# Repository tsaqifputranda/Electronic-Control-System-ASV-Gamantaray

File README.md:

# 🔧 Electronic (Control System) - ASV Gamantaray

Selamat datang di dokumentasi sistem kontrol elektronika kapal otonom Gamantaray.

## 📋 Daftar Isi Dokumentasi
1. **Project Overview** (Halaman Utama)
2. [Spesifikasi Sistem (Requirements)](./02_Requirements/requirements.md)
3. [Arsitektur & Diagram Blok](./03_System_Architecture/architecture.md)
4. [Desain Hardware & PCB](./04_Hardware_Design/hardware_desain.md)
5. [Power Management](./05_Power_Management/power_management.md)
6. [Wiring & Integration](./06_Wiring_&_Integration/integration_notes.md)
7. [Testing](./07_Testing/test_procedures.md)
8. [Problem & Solution](./08_Problem_&_Solution/troubleshooting.md)
9. [Final Evaluation](./09_Final_Evaluation/final_evaluation.md)
10. [Next Generation Notes](./10_Next_Generation_Notes/next_generation_notes.md)

---

## 🔌 Diagram Blok Sistem Utama
Untuk gambaran cepat mengenai interkoneksi sistem, kamu bisa melihat ringkasan diagram melalui tautan di bawah ini:

* ⚡ [Buka Diagram Blok Distribusi Daya Sistem Kontrol](./03_System_Architecture/PDB_Control_System_Diagram.jpg)
* 🗺️ [Buka Diagram Arsitektur Komunikasi Antar Komponen](./03_System_Architecture/Communication_Architecture_Diagram.jpg)

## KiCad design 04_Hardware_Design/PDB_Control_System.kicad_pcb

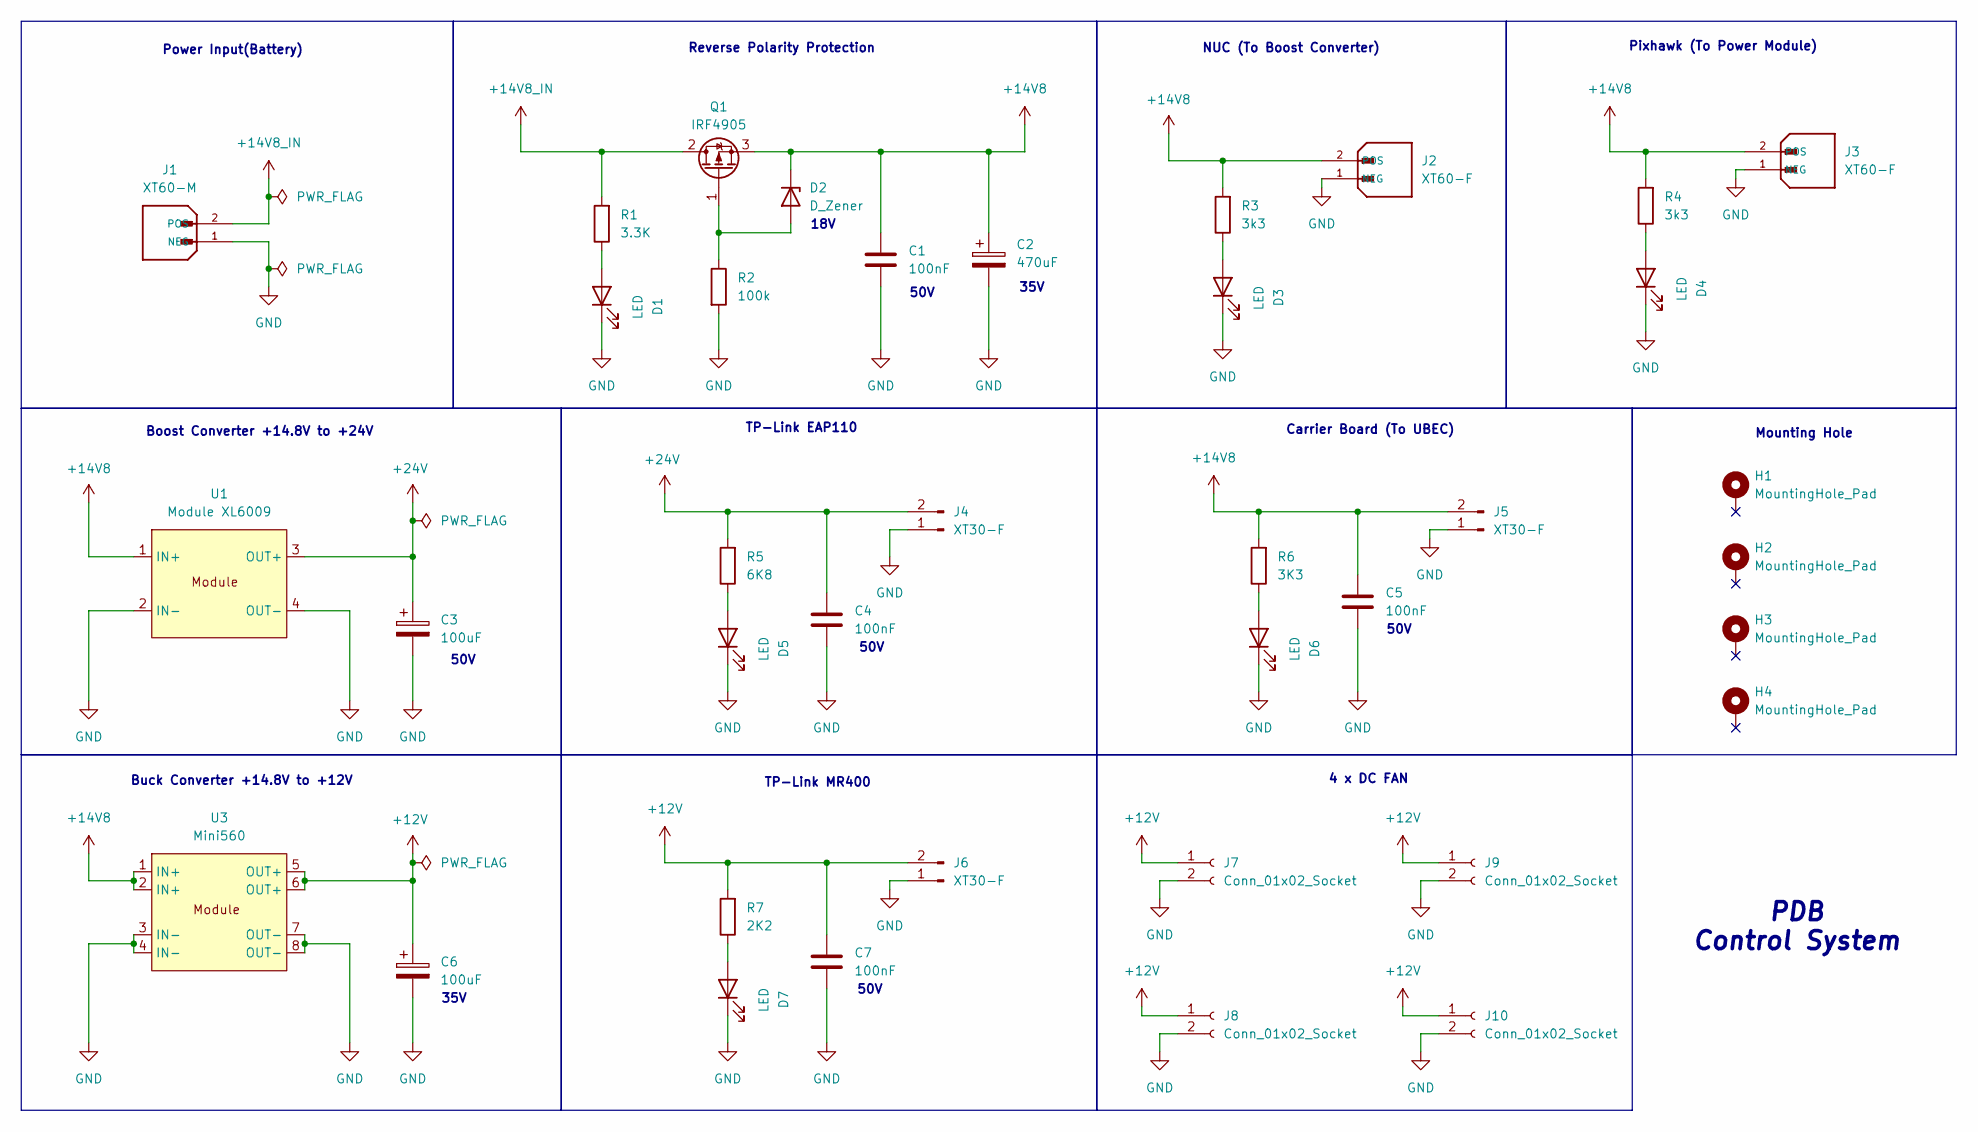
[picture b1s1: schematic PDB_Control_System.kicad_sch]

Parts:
C1, C4, C5, C7: 100nF; C_0805_2012Metric_Pad1.18x1.45mm_HandSolder
C2: 470uF; CP_Elec_10x10
C3, C6: 100uF; CP_Elec_6.3x5.4
D1, D3, D4, D5, D6, D7: LED; LED_0805_2012Metric_Pad1.15x1.40mm_HandSolder
D2: D_Zener; D_SOD-123
H1, H2, H3, H4: MountingHole_Pad; MountingHole_3.2mm_M3_Pad
J1: XT60-M; AMASS_XT60-M_1x02_P7.20mm_Vertical; PARTREV V1.2
J2, J3: XT60-F; AMASS_XT60-F_1x02_P7.20mm_Vertical
J4, J5, J6: XT30-F; AMASS_XT30U-F_1x02_P5.0mm_Vertical_custom
J7, J8, J9, J10: Conn_01x02_Socket; JST_XH_B2B-XH-A_1x02_P2.50mm_Vertical
Q1: IRF4905; TO-263-2
R1: 3.3K; R_0805_2012Metric_Pad1.20x1.40mm_HandSolder
R2: 100k; R_0805_2012Metric_Pad1.20x1.40mm_HandSolder
R3, R4: 3k3; R_0805_2012Metric_Pad1.20x1.40mm_HandSolder
R5: 6K8; R_0805_2012Metric_Pad1.20x1.40mm_HandSolder
R6: 3K3; R_0805_2012Metric_Pad1.20x1.40mm_HandSolder
R7: 2K2; R_0805_2012Metric_Pad1.20x1.40mm_HandSolder
U1: Module XL6009; XL6009 Module
U3: Mini560; Module Mini560

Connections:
+12V: C6.1, C7.1, J6.2, J7.1, J8.1, J9.1, J10.1, R7.2, U3.5 (OUT+), U3.6 (OUT+)
+14V8: C1.1, C2.1, C5.1, D2.1 (K), J2.2 (POS), J3.2 (POS), J5.2, Q1.3 (S), R3.2, R4.2, R6.2, U1.1 (IN+), U3.1 (IN+), U3.2 (IN+)
+14V8_IN: J1.2 (POS), Q1.2 (D), R1.2
+24V: C3.1, C4.1, J4.2, R5.2, U1.3 (OUT+)
GND: C1.2, C2.2, C3.2, C4.2, C5.2, C6.2, C7.2, D1.1 (K), D3.1 (K), D4.1 (K), D5.1 (K), D6.1 (K), D7.1 (K), J1.1 (NEG), J2.1 (NEG), J3.1 (NEG), J4.1, J5.1, J6.1, J7.2, J8.2, J9.2, J10.2, R2.2, U1.2 (IN-), U1.4 (OUT-), U3.3 (IN-), U3.4 (IN-), U3.7 (OUT-), U3.8 (OUT-)
unnamed: D1.2 (A), R1.1
unnamed: D2.2 (A), Q1.1 (G), R2.1
unnamed: D3.2 (A), R3.1
unnamed: D4.2 (A), R4.1
unnamed: D5.2 (A), R5.1
unnamed: D6.2 (A), R6.1
unnamed: D7.2 (A), R7.1

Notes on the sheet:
50V
18V
NUC (To Boost Converter)
Buck Converter +14.8V to +12V
4 x DC FAN
Boost Converter +14.8V to +24V
TP-Link EAP110
35V
Mounting Hole
Pixhawk (To Power Module)
Reverse Polarity Protection
PDB Control System
Power Input(Battery)
Carrier Board (To UBEC)
TP-Link MR400

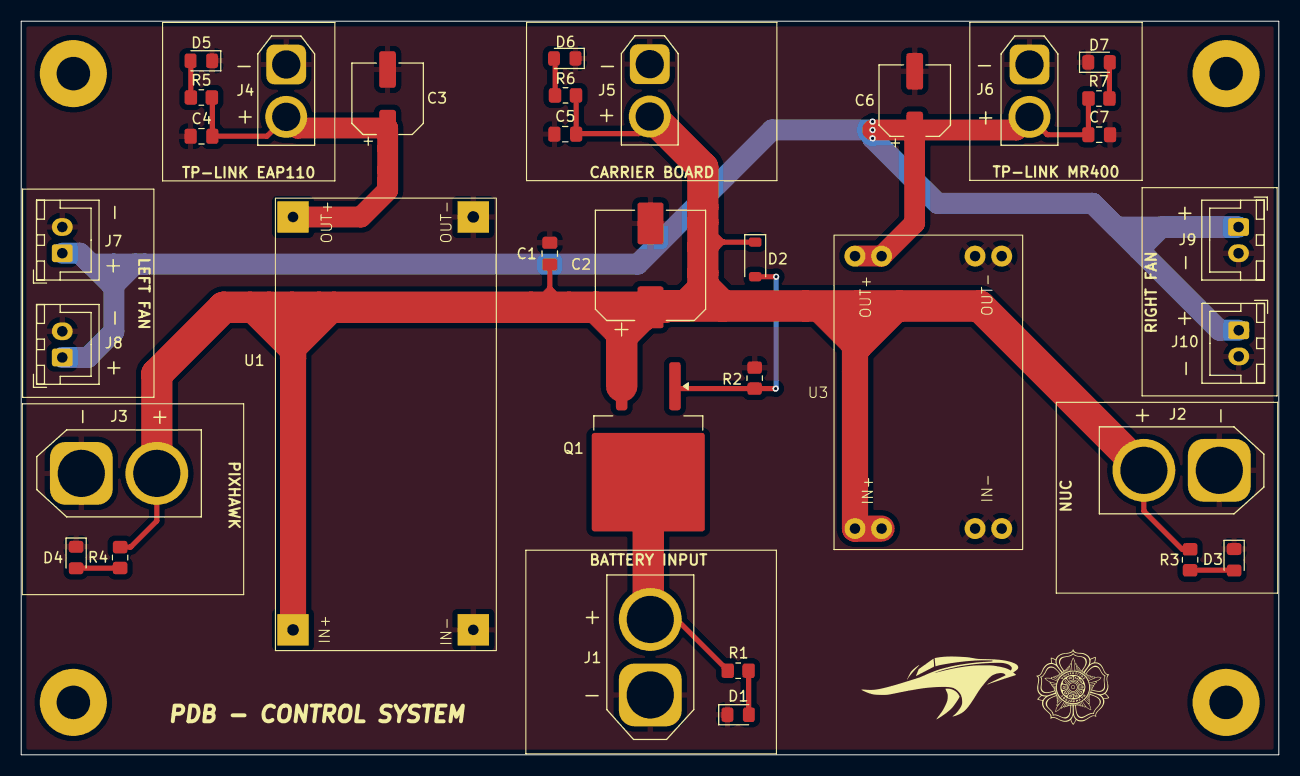
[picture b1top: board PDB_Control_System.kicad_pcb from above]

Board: 2 copper layers, 120.0 x 70.0 mm, 38 parts (0 on the bottom side), 12 nets.

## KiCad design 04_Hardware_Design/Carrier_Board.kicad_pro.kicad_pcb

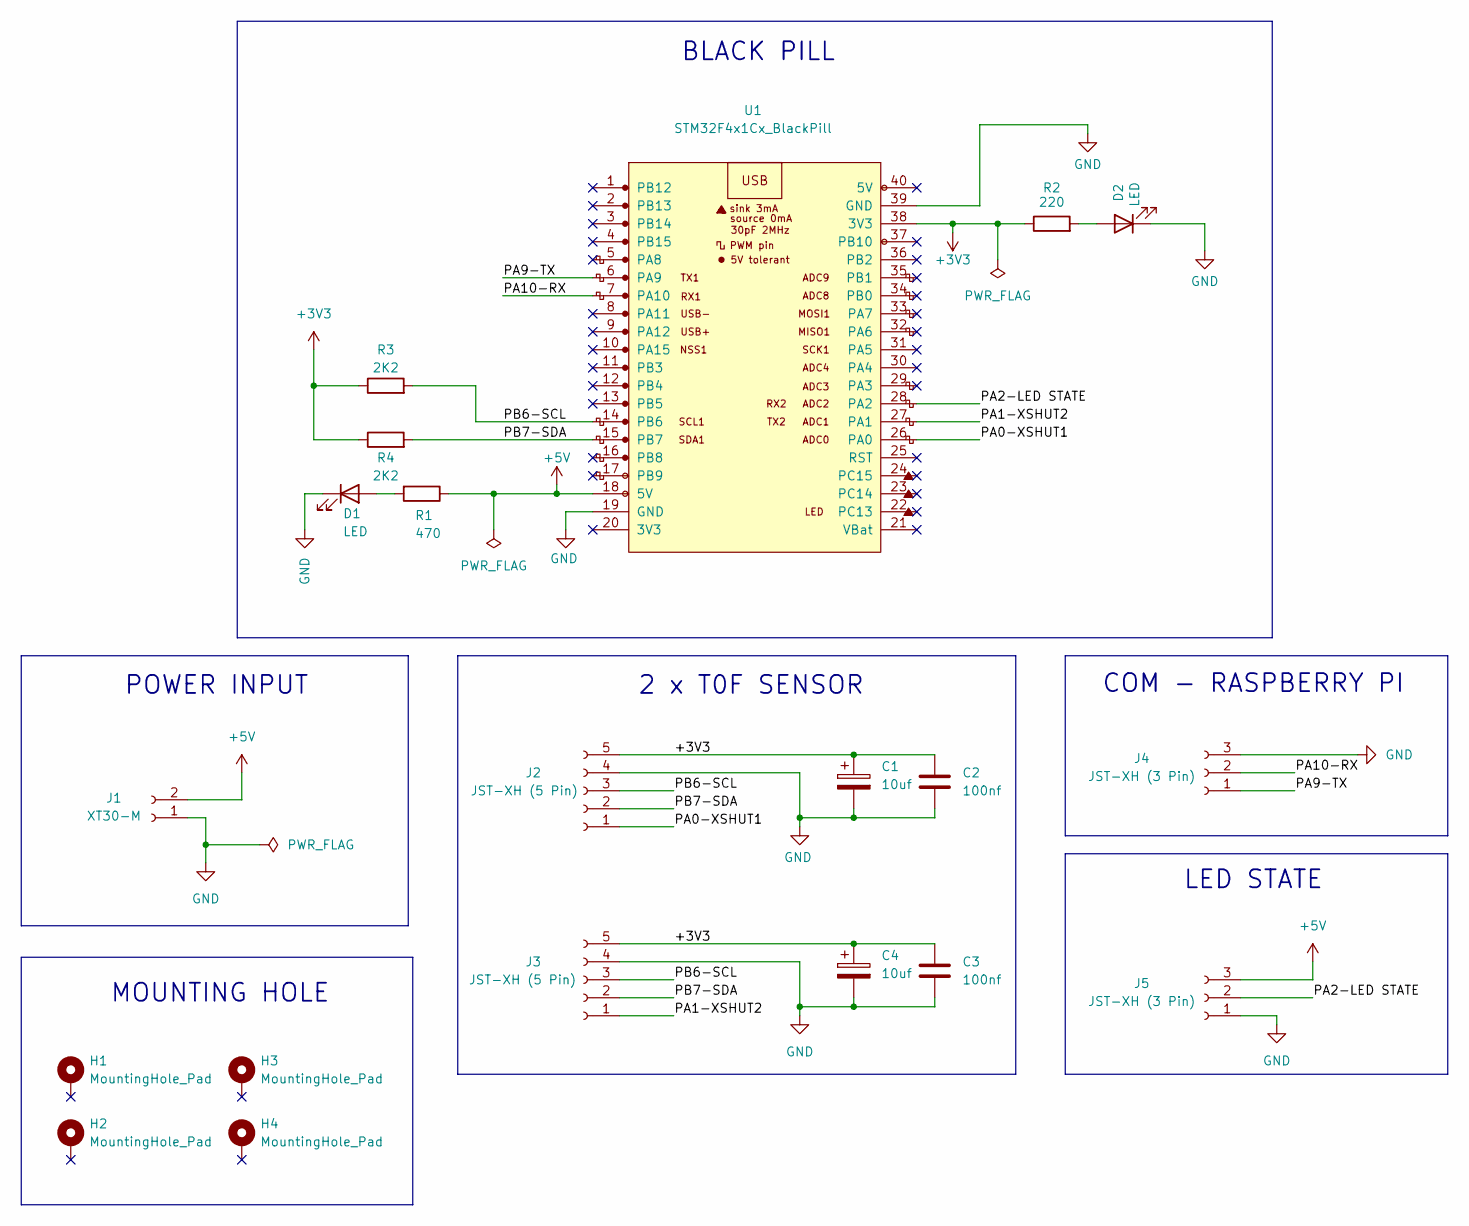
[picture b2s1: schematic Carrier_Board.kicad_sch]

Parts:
C1, C4: 10uf; CP_Elec_4x5.3
C2, C3: 100nf; C_0805_2012Metric_Pad1.18x1.45mm_HandSolder
D1, D2: LED; LED_0805_2012Metric
H1, H2, H3, H4: MountingHole_Pad; MountingHole_3.2mm_M3_Pad
J1: XT30-M; AMASS_XT30U-M_1x02_P5.0mm_Vertical
J2, J3: JST-XH (5 Pin); JST_XH_B5B-XH-A_1x05_P2.50mm_Vertical
J4, J5: JST-XH (3 Pin); JST_XH_B3B-XH-A_1x03_P2.50mm_Vertical
R1: 470; R_0805_2012Metric_Pad1.20x1.40mm_HandSolder
R2: 220; R_0805_2012Metric_Pad1.20x1.40mm_HandSolder
R3, R4: 2K2; R_0805_2012Metric_Pad1.20x1.40mm_HandSolder
U1: STM32F4x1Cx_BlackPill; STM32F4x1Cx_BlackPill_PartLike

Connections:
+3V3: C1.1, C2.1, C3.1, C4.1, J2.5, J3.5, R2.1, R3.1, R4.1, U1.38 (3V3)
+5V: J1.2, J5.3, R1.1, U1.18 (5V)
/PA0-XSHUT1: J2.1, U1.26 (PA0)
/PA1-XSHUT2: J3.1, U1.27 (PA1)
/PA2-LED STATE: J5.2, U1.28 (PA2)
/PA9-TX: J4.1, U1.6 (PA9)
/PA10-RX: J4.2, U1.7 (PA10)
/PB6-SCL: J2.3, J3.3, R3.2, U1.14 (PB6)
/PB7-SDA: J2.2, J3.2, R4.2, U1.15 (PB7)
GND: C1.2, C2.2, C3.2, C4.2, D1.1 (K), D2.1 (K), J1.1, J2.4, J3.4, J4.3, J5.1, U1.19 (GND), U1.39 (GND)
unnamed: D1.2 (A), R1.2
unnamed: D2.2 (A), R2.2

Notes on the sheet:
COM - RASPBERRY PI
POWER INPUT
MOUNTING HOLE
LED STATE
2 x T0F SENSOR
BLACK PILL

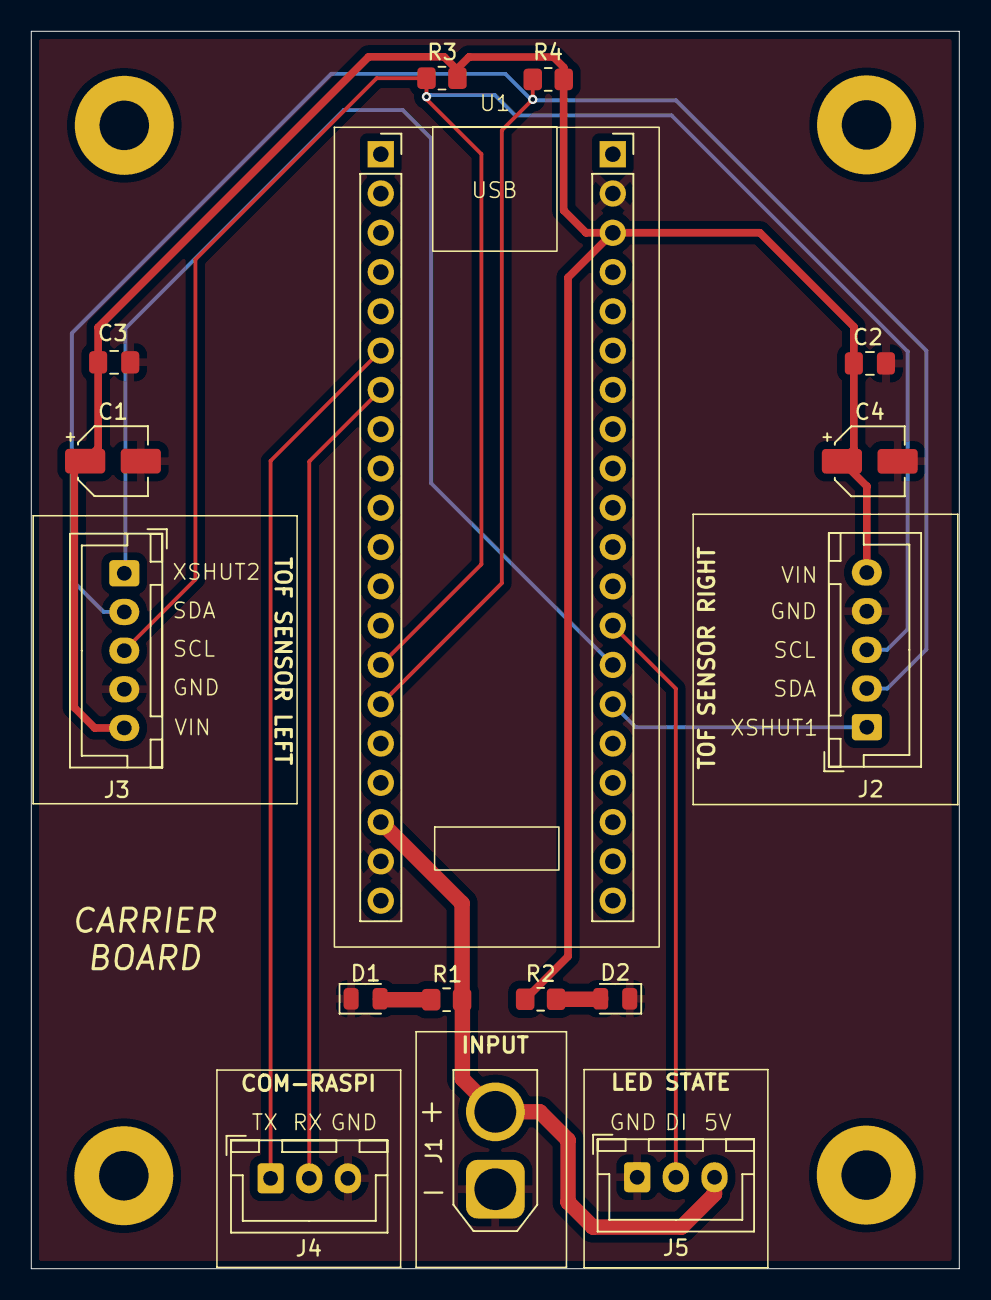
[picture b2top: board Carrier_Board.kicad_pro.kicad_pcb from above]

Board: 2 copper layers, 60.0 x 80.0 mm, 20 parts (0 on the bottom side), 12 nets.
